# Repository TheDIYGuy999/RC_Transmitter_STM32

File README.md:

# This is an Arduino 2.4GHz radio and IR transmitter for STM32
## Features:
- IR transmitter for "LEGO" Powerfunctions and trains as well as for "MECCANO" motors
- 2.4GHz radio transmitter for RC cars, helicopters etc.
- 4 analog axes, 2 mode switches (joystick buttons)
- 1 potentiometer for adjustments like the MRSC stability control
- 4 push buttons for transmission mode and vehicle selection as well as menu navigation
- 10 seletcable vehicle addresses, so you can use it for more than one vehicle
- 3.3V, 72MHz STM32F103C8T6 ARM board
- Atmel AVR version see: https://github.com/TheDIYGuy999/RC_Transmitter
- 2.4GHz NRF24L01 radio module
- Support for 0.96" I2C OLED.
- Configuration menu for: Channel direction reversing, servo travel adjustment (independent for each vehicle)
- Configuration values are stored in EEPROM
- NRF24L01+PA+LNA SMA radio modules with power amplifier are supported from board version 1.1
- very compact
- Eagle schematic will follow
- PONG Game included (runs much faster than on the Atmel AVR version)

## Changelog:

New in V 2.0:
- Initial commit starting with V2.0, because the features are the same as in V2.0 for Atmel ARM MCU's
- Pinout according to the software comments. An Eagle schematic will follow later
- Works together with my Atmel AVR based receivers or the transmitter in "Tester Mode"
- OLED now driven by the u8g2 library in "full buffer" mode. This is much faster, but requires more RAM (no problem on the STM32)
- Lego IR ist tested
- Meccano IR should work in theory, but the signal was only tested with an oscilloscope
- The emulated STM32 EEPROM seems to work properly, but the required "eepromHandler.h" is entirely new
- This version may still contain bugs. It was only tested on a breadboard

New in V 2.01:
- Battery voltage detection bug fixed

## Usage

See pictures

The biggest and the smallest vehicle:

The Atmel AVR version:

The STM32 test rig on a breadboard:

(c) 2017 TheDIYGuy999

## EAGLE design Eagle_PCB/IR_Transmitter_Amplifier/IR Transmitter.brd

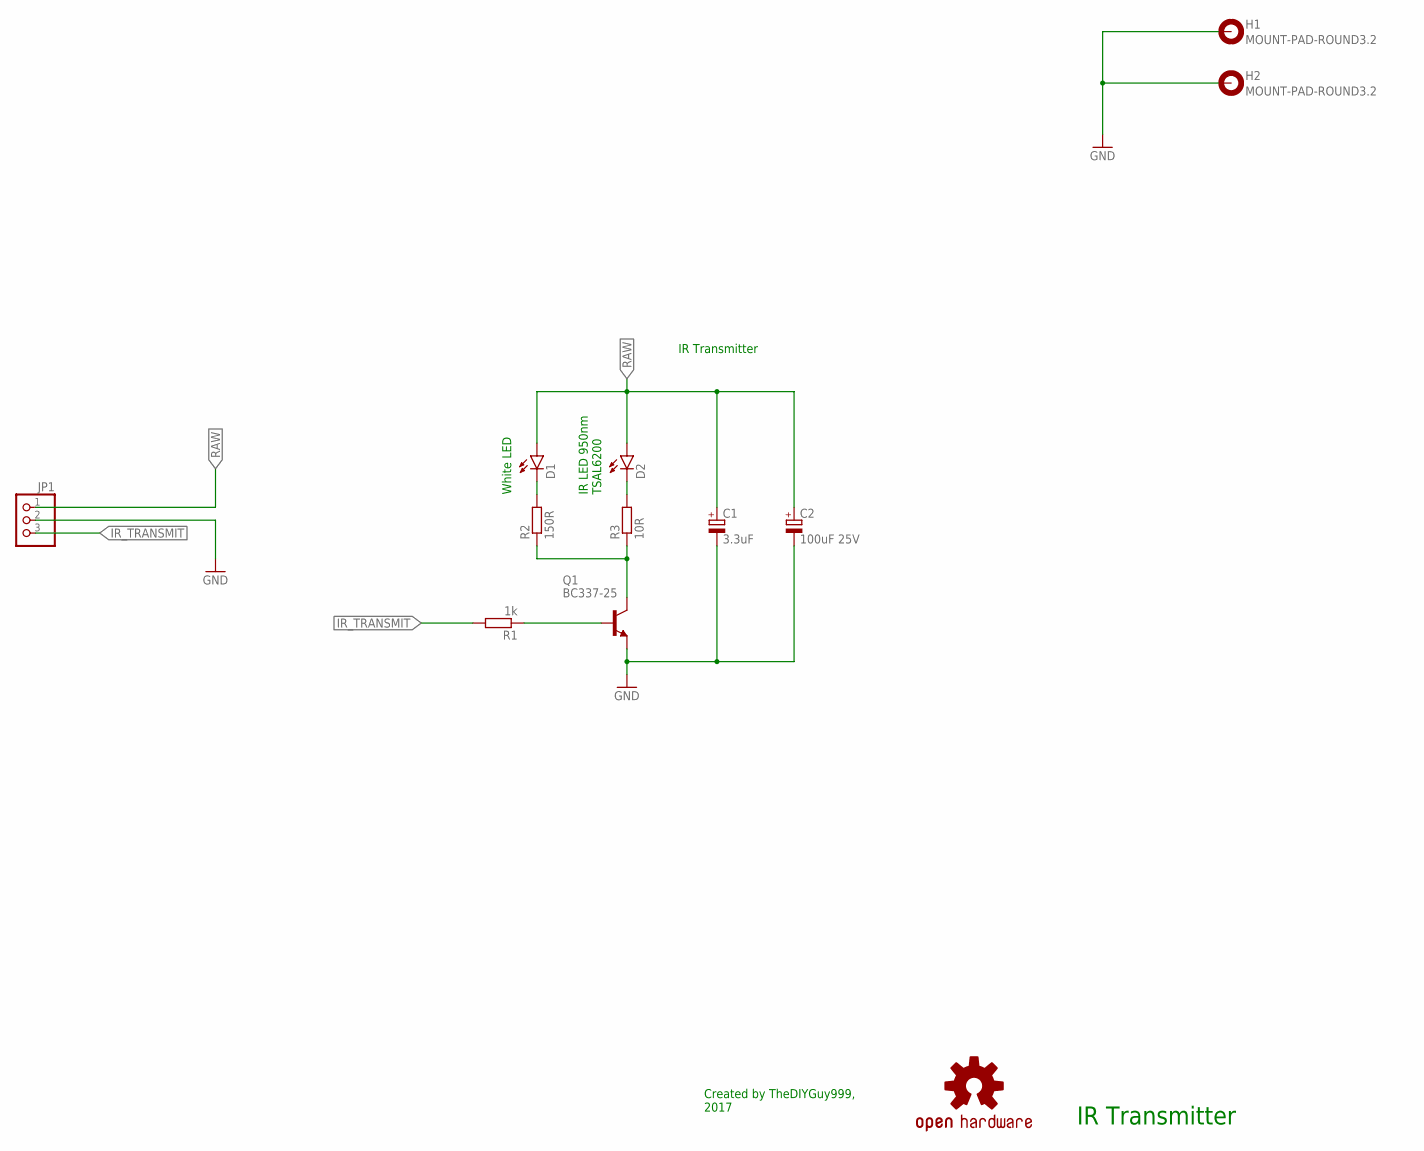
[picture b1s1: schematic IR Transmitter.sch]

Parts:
C1: 3.3uF; B45181A
C2: 100uF 25V; E2,5-7
D1, D2: LED5MM
H1, H2: MOUNT-PAD-ROUND3.2; 3,2-PAD
JP1: PINHD-1X3; 1X03
LOGO1: OSHW-LOGOM; OSHW-LOGO-M
Q1: BC337-25; TO92
R1: 1k; 0207/2V
R2: 150R; 0207/2V
R3: 10R; 0207/2V

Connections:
GND: C1.-, C2.-, H1.B3,2, H2.B3,2, JP1.2, Q1.1 (E)
IR_TRANSMIT: JP1.3, R1.2
unnamed: Q1.3 (C), R2.1, R3.1
unnamed: D2.K (C), R3.2
unnamed: Q1.2 (B), R1.1
unnamed: D1.K (C), R2.2
RAW: C1.+, C2.+, D1.A, D2.A, JP1.1

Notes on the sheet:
IR Transmitter
White LED
IR LED 950nm TSAL6200
Created by TheDIYGuy999, 2017

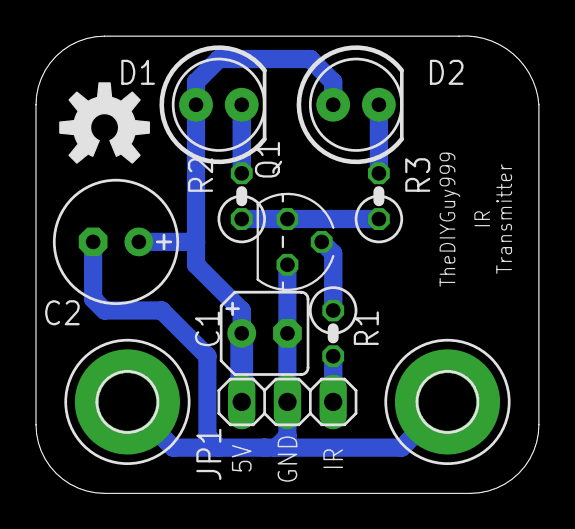
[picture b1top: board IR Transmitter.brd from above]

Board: 2 copper layers, 27.9 x 25.4 mm, 12 parts (0 on the bottom side), 7 nets.

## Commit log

2017-12-11 Initial commit: V2.0 (as the AVR version)
2017-12-13 Create Test
2017-12-13 Schematic, board file will follow later
2017-12-18 V2.01: Battery voltage detection bug fixed
2017-12-19 Small IR transmitter with amplifier

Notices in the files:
parts and their libraries:
SparkFun-LED: Licensing: Creative Commons ShareAlike 4.0 International - https://creativecommons.org/licenses/by-sa/4.0
